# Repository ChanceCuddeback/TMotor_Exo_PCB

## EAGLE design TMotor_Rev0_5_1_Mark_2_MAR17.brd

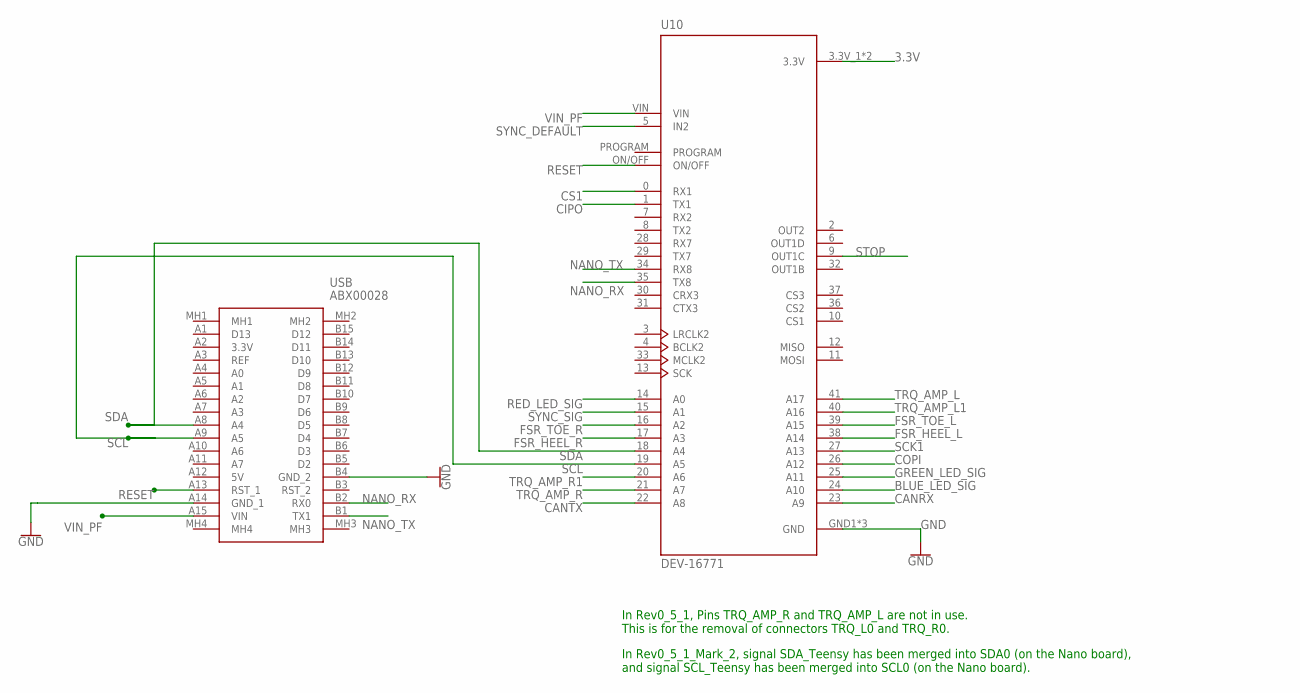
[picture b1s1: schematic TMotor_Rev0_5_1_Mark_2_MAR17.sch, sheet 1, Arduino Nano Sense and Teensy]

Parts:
U10: DEV-16771; MODULE_DEV-16771
USB: ABX00028

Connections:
3.3V: U10.3.3V_1 (3.3V), U10.3.3V_2 (3.3V); also elsewhere on the board
BLUE_LED_SIG: U10.24 (A10); also elsewhere on the board
CANRX: U10.23 (A9); also elsewhere on the board
CANTX: U10.22 (A8); also elsewhere on the board
CIPO: U10.1 (TX1); also elsewhere on the board
COPI: U10.26 (A12); also elsewhere on the board
CS1: U10.0 (RX1); also elsewhere on the board
FSR_HEEL_L: U10.38 (A14); also elsewhere on the board
FSR_HEEL_R: U10.17 (A3); also elsewhere on the board
FSR_TOE_L: U10.39 (A15); also elsewhere on the board
FSR_TOE_R: U10.16 (A2); also elsewhere on the board
GND: U10.GND1 (GND), U10.GND2 (GND), U10.GND3 (GND), USB.A14 (GND_1), USB.B4 (GND_2); also elsewhere on the board
GREEN_LED_SIG: U10.25 (A11); also elsewhere on the board
NANO_RX: U10.35 (TX8), USB.B2 (RX0)
NANO_TX: U10.34 (RX8), USB.B1 (TX1)
RED_LED_SIG: U10.14 (A0); also elsewhere on the board
RESET: U10.ON/OFF, USB.A13 (RST_1); also elsewhere on the board
SCK1: U10.27 (A13); also elsewhere on the board
SCL: U10.19 (A5), USB.A9 (A5); also elsewhere on the board
SDA: U10.18 (A4), USB.A8 (A4); also elsewhere on the board
STOP: U10.9 (OUT1C); also elsewhere on the board
SYNC_DEFAULT: U10.5 (IN2); also elsewhere on the board
SYNC_SIG: U10.15 (A1); also elsewhere on the board
TRQ_AMP_L: U10.41 (A17)
TRQ_AMP_L1: U10.40 (A16); also elsewhere on the board
TRQ_AMP_R: U10.21 (A7)
TRQ_AMP_R1: U10.20 (A6); also elsewhere on the board
VIN_PF: U10.VIN, USB.A15 (VIN); also elsewhere on the board

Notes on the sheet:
In Rev0_5_1, Pins TRQ_AMP_R and TRQ_AMP_L are not in use. This is for the removal of connectors TRQ_L0 and TRQ_R0.
In Rev0_5_1_Mark_2, signal SDA_Teensy has been merged into SDA0 (on the Nano board), and signal SCL_Teensy has been merged into SCL0 (on the Nano board).

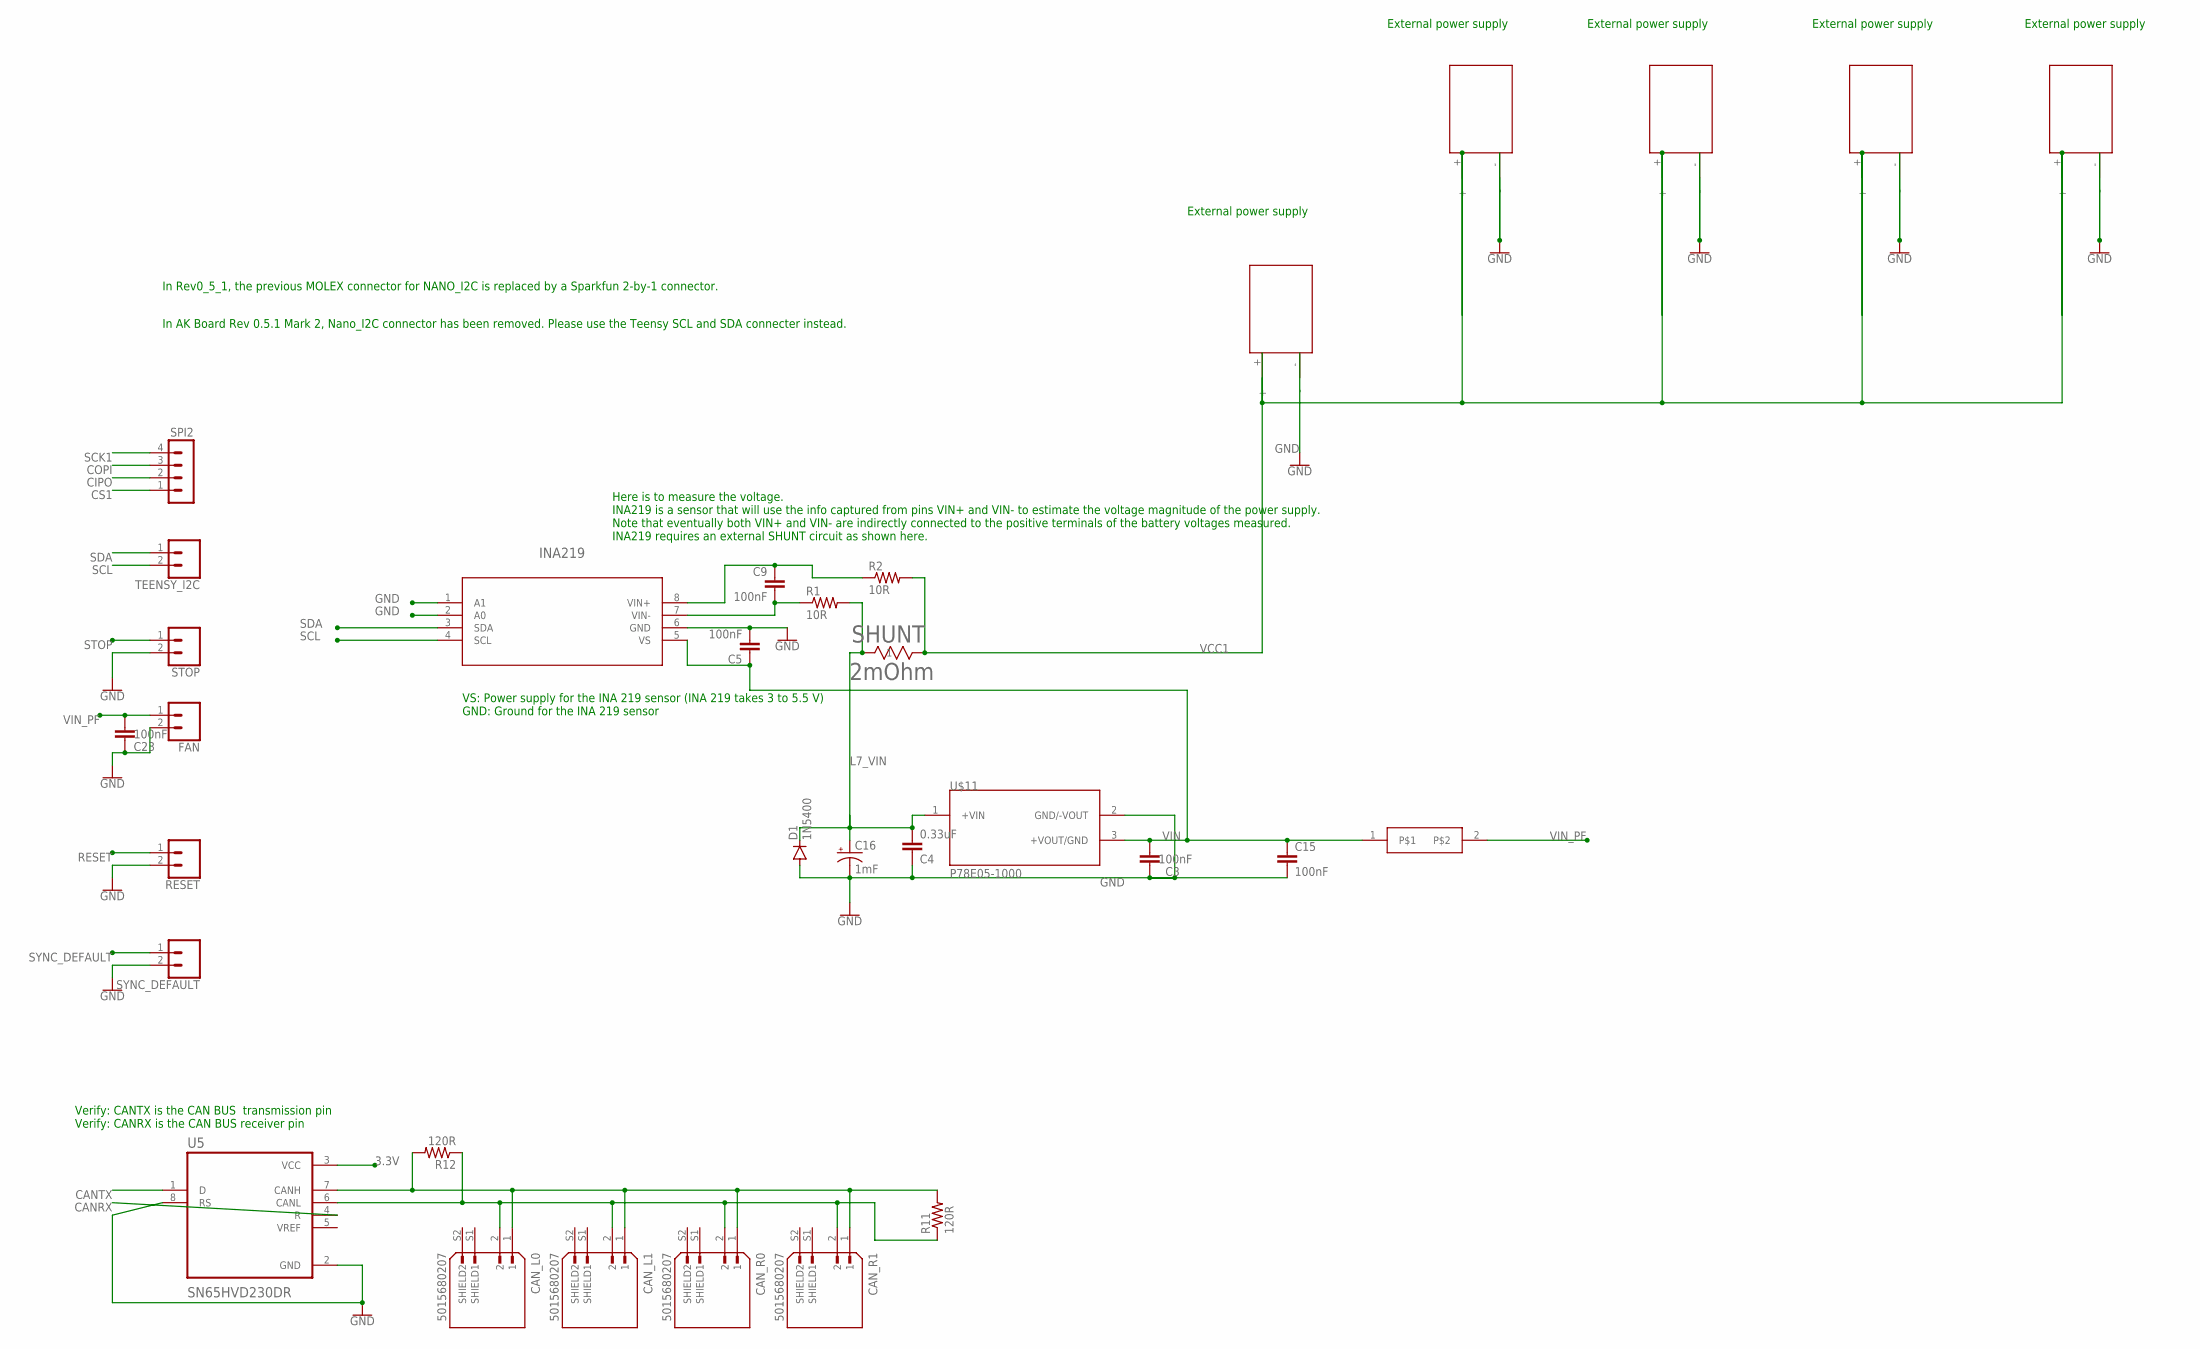
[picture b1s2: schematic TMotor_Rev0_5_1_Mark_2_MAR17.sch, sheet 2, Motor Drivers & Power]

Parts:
C3, C5, C9, C15, C23: 100nF; C050-024X044
C4: 0.33uF; C050-024X044
C16: 1mF; E5-10,5
CAN_L0, CAN_L1: 5015680207; MOLEX_5015680207
CAN_R0, CAN_R1: 5015680207; MOLEX_5015680207
D1: 1N5400; DO201-15
FAN: CONN_02; 1X02
INA219: D8_TEX
R1, R2: 10R; 0207/10
R11, R12: 120R; 0207/10
RESET: CONN_02; 1X02
SHUNT: 2mOhm; STA_CSNL2512(2)_STP
SPI2: MA04-1
STOP: CONN_02; 1X02
SYNC_DEFAULT: CONN_02; 1X02
TEENSY_I2C: CONN_02; 1X02
U5: SN65HVD230DR; SOIC127P599X175-8N
U$6: 0458002.DR; FUSE_LITTEL_448
U$11: P78E05-1000
XT30UPB-F, XT30UPB-F1, XT30UPB-F2, XT30UPB-F3, XT30UPB-F4: L_0; XT30UPB-F

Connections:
3.3V: U5.3 (VCC); also elsewhere on the board
CANRX: U5.4 (R); also elsewhere on the board
CANTX: U5.1 (D); also elsewhere on the board
CIPO: SPI2.2; also elsewhere on the board
COPI: SPI2.3; also elsewhere on the board
CS1: SPI2.1; also elsewhere on the board
GND: C3.1, C4.1, C5.2, C15.2, C16.-, C23.1, D1.A, FAN.2, INA219.1 (A1), INA219.2 (A0), INA219.6 (GND), RESET.2, STOP.2, SYNC_DEFAULT.2, U5.2 (GND), U5.8 (RS), U$11.2 (GND/-VOUT), XT30UPB-F.-, XT30UPB-F1.-, XT30UPB-F2.-, XT30UPB-F3.-, XT30UPB-F4.-; also elsewhere on the board
L7_VIN: C4.2, C16.+, D1.C, R1.2, SHUNT.1, U$11.1 (+VIN)
unnamed: C9.1, INA219.8 (VIN+), R2.1
unnamed: C9.2, INA219.7 (VIN-), R1.1
unnamed: CAN_L0.1, CAN_L1.1, CAN_R0.1, CAN_R1.1, R11.2, R12.2, U5.7 (CANH)
unnamed: CAN_L0.2, CAN_L1.2, CAN_R0.2, CAN_R1.2, R11.1, R12.1, U5.6 (CANL)
RESET: RESET.1; also elsewhere on the board
SCK1: SPI2.4; also elsewhere on the board
SCL: INA219.4 (SCL), TEENSY_I2C.2; also elsewhere on the board
SDA: INA219.3 (SDA), TEENSY_I2C.1; also elsewhere on the board
STOP: STOP.1; also elsewhere on the board
SYNC_DEFAULT: SYNC_DEFAULT.1; also elsewhere on the board
VCC1: R2.2, SHUNT.2, XT30UPB-F.+, XT30UPB-F1.+, XT30UPB-F2.+, XT30UPB-F3.+, XT30UPB-F4.+
VIN: C3.2, C5.1, C15.1, INA219.5 (VS), U$6.1, U$11.3 (+VOUT/GND)
VIN_PF: C23.2, FAN.1, U$6.2; also elsewhere on the board

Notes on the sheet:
External power supply
Here is to measure the voltage. INA219 is a sensor that will use the info captured from pins VIN+ and VIN- to estimate the voltage magnitude of the power supply. Note that eventually both VIN+ and VIN- are indirectly connected to the positive terminals of the battery voltages measured. INA219 requi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
VS: Power supply for the INA 219 sensor (INA 219 takes 3 to 5.5 V) GND: Ground for the INA 219 sensor
Verify: CANTX is the CAN BUS transmission pin Verify: CANRX is the CAN BUS receiver pin
In Rev0_5_1, the previous MOLEX connector for NANO_I2C is replaced by a Sparkfun 2-by-1 connector.
In AK Board Rev 0.5.1 Mark 2, Nano_I2C connector has been removed. Please use the Teensy SCL and SDA connecter instead.

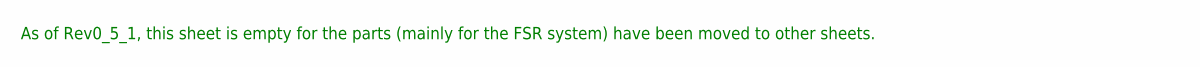
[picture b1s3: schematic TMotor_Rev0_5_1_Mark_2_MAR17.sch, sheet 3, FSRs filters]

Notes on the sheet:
As of Rev0_5_1, this sheet is empty for the parts (mainly for the FSR system) have been moved to other sheets.

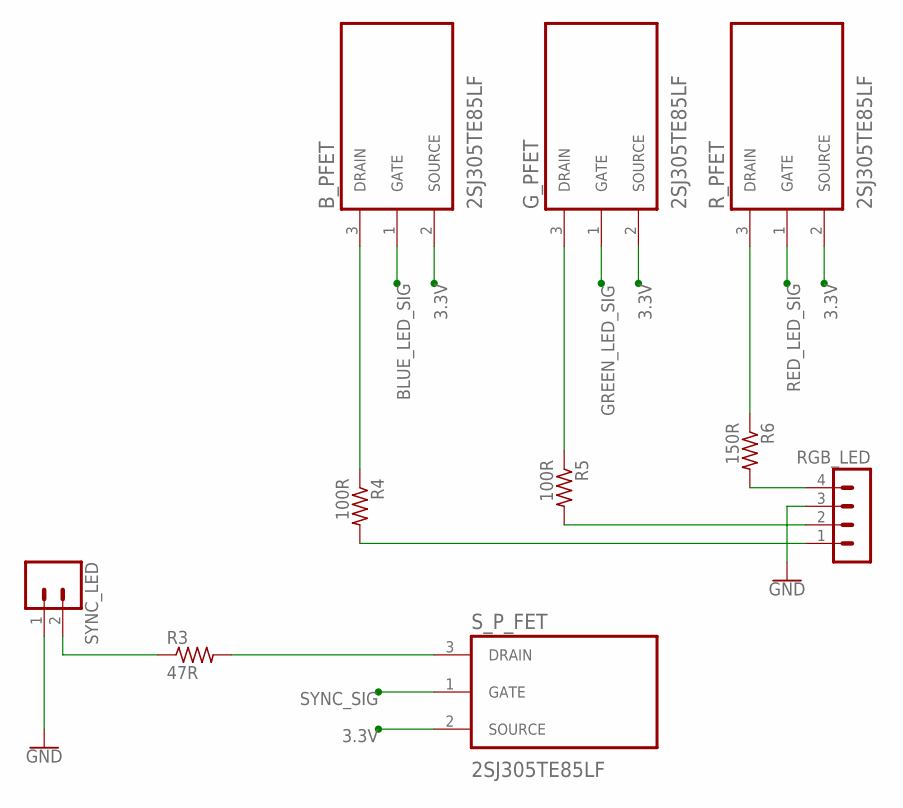
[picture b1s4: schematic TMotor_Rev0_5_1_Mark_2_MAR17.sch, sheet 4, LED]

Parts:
B_PFET: 2SJ305TE85LF; TRANS_SSM3J325F,LF
G_PFET: 2SJ305TE85LF; TRANS_SSM3J325F,LF
R3: 47R; 0207/10
R4, R5: 100R; 0207/10
R6: 150R; 0207/10
RGB_LED: MA04-1
R_PFET: 2SJ305TE85LF; TRANS_SSM3J325F,LF
SYNC_LED: CONN_02; 1X02
S_P_FET: 2SJ305TE85LF; TRANS_SSM3J325F,LF

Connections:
3.3V: B_PFET.2 (SOURCE), G_PFET.2 (SOURCE), R_PFET.2 (SOURCE), S_P_FET.2 (SOURCE); also elsewhere on the board
BLUE_LED_SIG: B_PFET.1 (GATE); also elsewhere on the board
GND: RGB_LED.3, SYNC_LED.1; also elsewhere on the board
GREEN_LED_SIG: G_PFET.1 (GATE); also elsewhere on the board
unnamed: R4.2, RGB_LED.1
unnamed: B_PFET.3 (DRAIN), R4.1
unnamed: R3.2, S_P_FET.3 (DRAIN)
unnamed: R3.1, SYNC_LED.2
unnamed: R6.2, RGB_LED.4
unnamed: R5.2, RGB_LED.2
unnamed: G_PFET.3 (DRAIN), R5.1
unnamed: R6.1, R_PFET.3 (DRAIN)
RED_LED_SIG: R_PFET.1 (GATE); also elsewhere on the board
SYNC_SIG: S_P_FET.1 (GATE); also elsewhere on the board

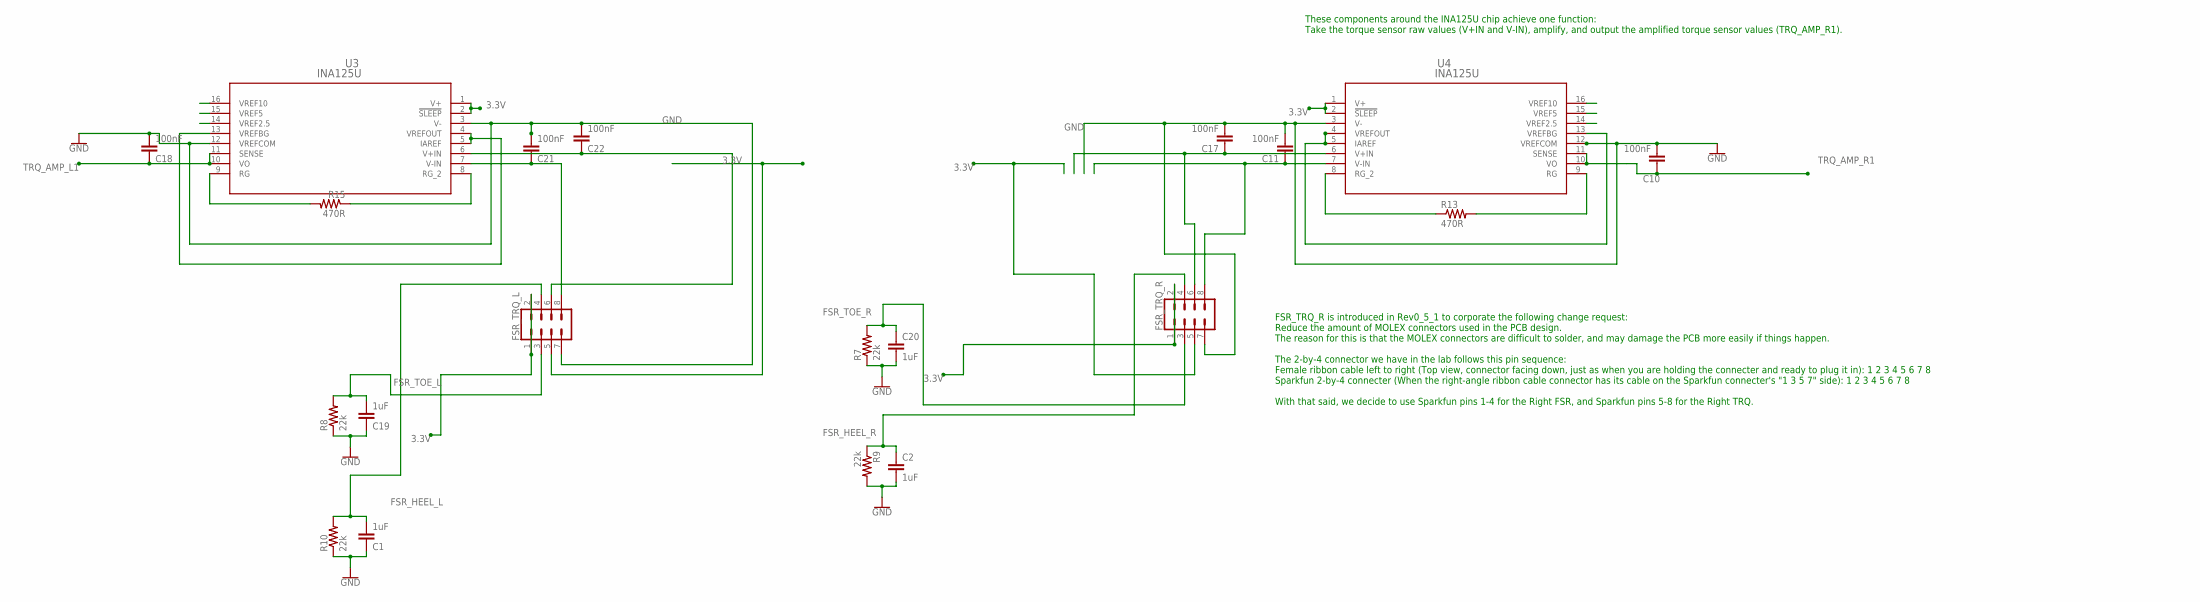
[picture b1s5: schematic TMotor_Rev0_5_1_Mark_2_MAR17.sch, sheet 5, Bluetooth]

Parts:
C1, C2, C19, C20: 1uF; C050-024X044
C10, C11, C17, C18, C21, C22: 100nF; C050-024X044
FSR_TRQ_L: CONN_04X2; 2X4
FSR_TRQ_R: CONN_04X2; 2X4
R7, R8, R9, R10: 22k; 0207/10
R13, R15: 470R; 0207/10
U3, U4: INA125U; D16

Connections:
3.3V: FSR_TRQ_L.1, FSR_TRQ_L.2, FSR_TRQ_L.5, FSR_TRQ_R.1, FSR_TRQ_R.2, FSR_TRQ_R.5, U3.1 (V+), U3.2 (!SLEEP), U4.1 (V+), U4.2 (!SLEEP); also elsewhere on the board
FSR_HEEL_L: C1.2, FSR_TRQ_L.4, R10.2; also elsewhere on the board
FSR_HEEL_R: C2.1, FSR_TRQ_R.4, R9.1; also elsewhere on the board
FSR_TOE_L: C19.2, FSR_TRQ_L.3, R8.2; also elsewhere on the board
FSR_TOE_R: C20.1, FSR_TRQ_R.3, R7.2; also elsewhere on the board
GND: C1.1, C2.2, C10.2, C11.2, C17.2, C18.2, C19.1, C20.2, C21.2, C22.2, FSR_TRQ_L.7, FSR_TRQ_R.7, R7.1, R8.1, R9.2, R10.1, U3.3 (V-), U3.12 (VREFCOM), U4.3 (V-), U4.12 (VREFCOM); also elsewhere on the board
unnamed: U4.4 (VREFOUT), U4.5 (IAREF), U4.13 (VREFBG)
unnamed: R13.1, U4.8 (RG_2)
unnamed: R13.2, U4.9 (RG)
unnamed: C17.1, FSR_TRQ_R.6, U4.6 (V+IN)
unnamed: C11.1, FSR_TRQ_R.8, U4.7 (V-IN)
unnamed: U3.4 (VREFOUT), U3.5 (IAREF), U3.13 (VREFBG)
unnamed: C22.1, FSR_TRQ_L.6, U3.6 (V+IN)
unnamed: C21.1, FSR_TRQ_L.8, U3.7 (V-IN)
unnamed: R15.2, U3.9 (RG)
unnamed: R15.1, U3.8 (RG_2)
TRQ_AMP_L1: C18.1, U3.10 (VO), U3.11 (SENSE); also elsewhere on the board
TRQ_AMP_R1: C10.1, U4.10 (VO), U4.11 (SENSE); also elsewhere on the board

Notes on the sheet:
FSR_TRQ_R is introduced in Rev0_5_1 to corporate the following change request: Reduce the amount of MOLEX connectors used in the PCB design. The reason for this is that the MOLEX connectors are difficult to solder, and may damage the PCB more easily if things happen. The 2-by-4 connector we have in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
These components around the INA125U chip achieve one function: Take the torque sensor raw values (V+IN and V-IN), amplify, and output the amplified torque sensor values (TRQ_AMP_R1).

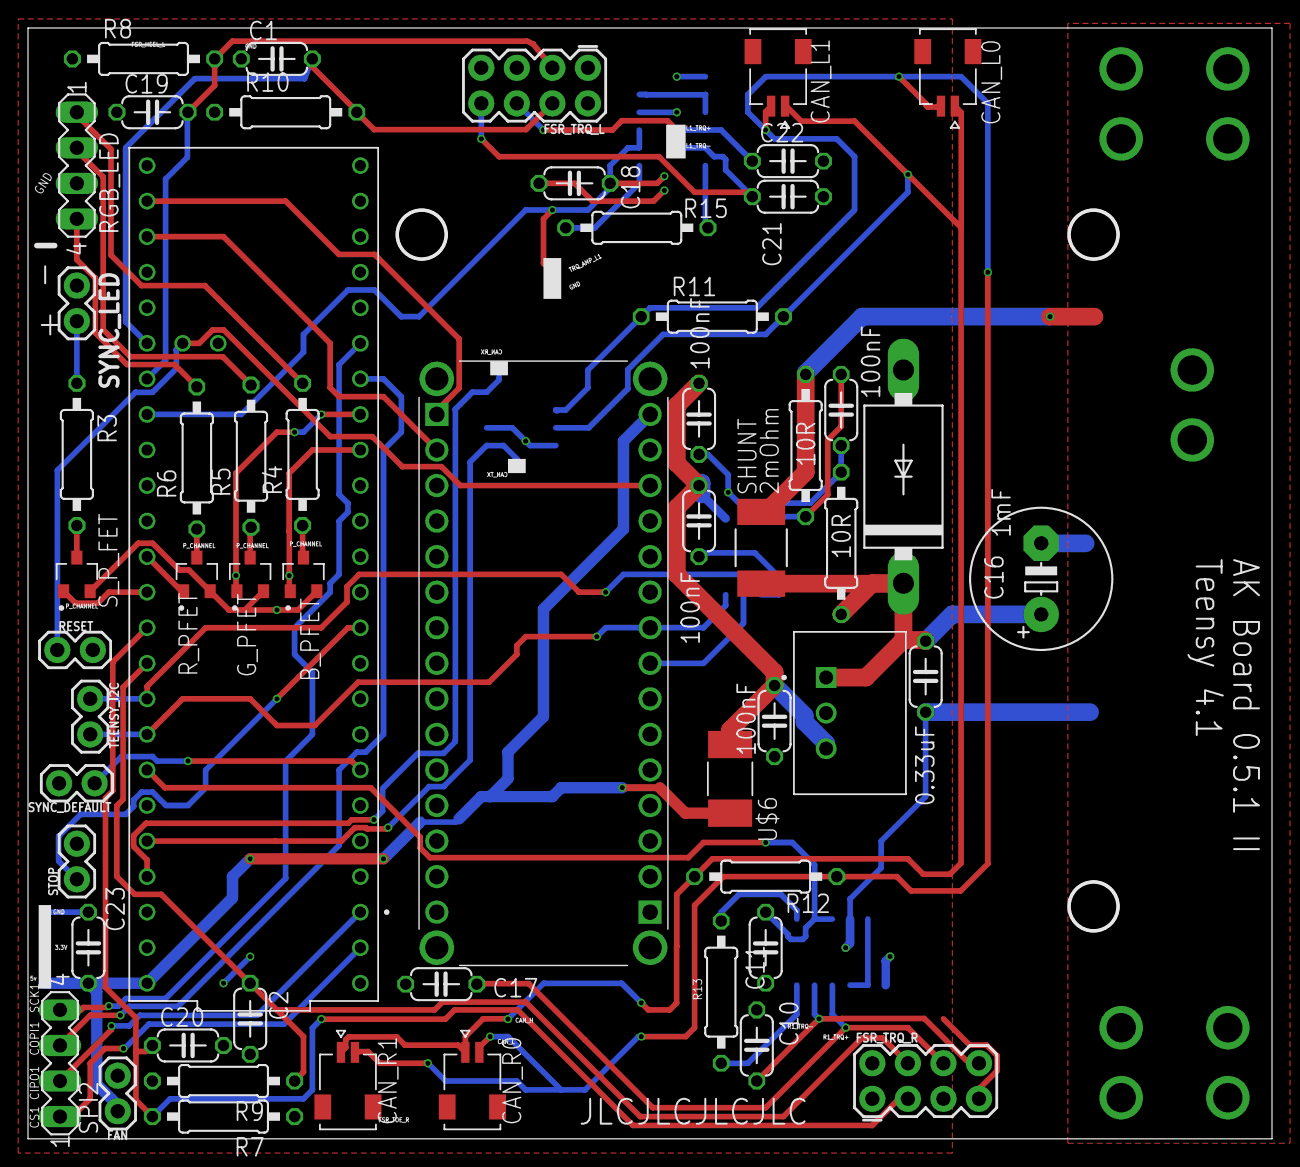
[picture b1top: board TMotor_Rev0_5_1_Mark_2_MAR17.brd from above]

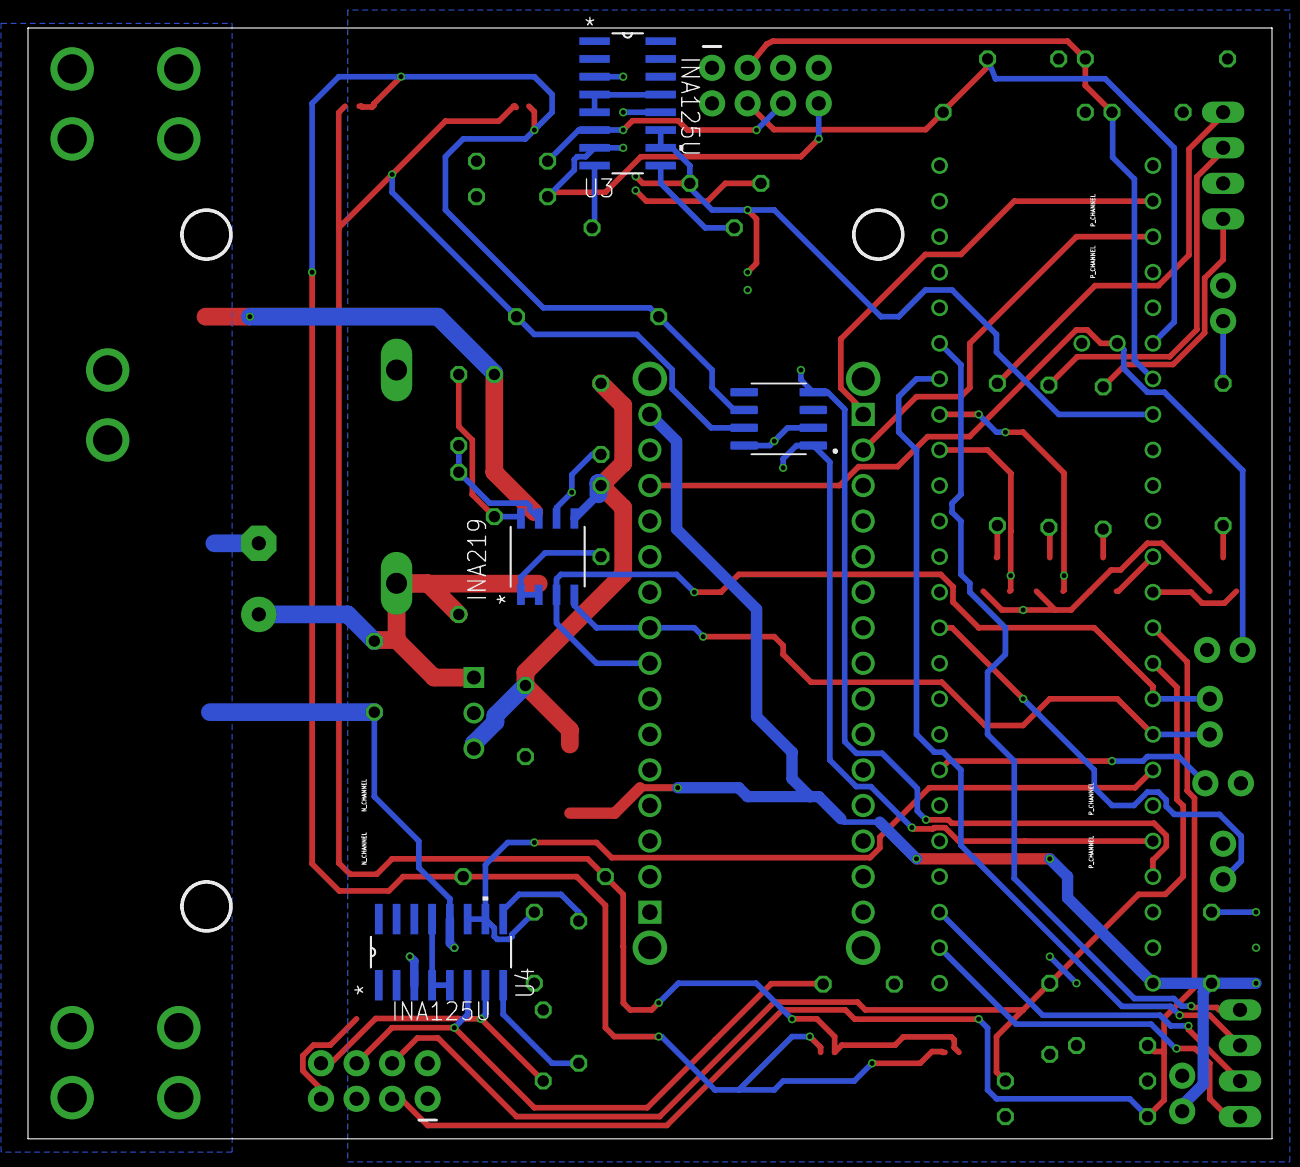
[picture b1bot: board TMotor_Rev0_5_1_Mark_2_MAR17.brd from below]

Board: 2 copper layers, 88.6 x 79.1 mm, 64 parts (4 on the bottom side), 51 nets.

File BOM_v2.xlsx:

Comments | Designator | Footprint | JLCPCB Part #（optional）
2SJ305TE85LF | B_PFET | 2SJ305TE85LF | C694088
1uF | C1 | C-EU050-024X044 | C263187
1uF | C2 | C-EU050-024X044 | C263187
100nF | C3 | C-EU050-024X044 | C110282
0.33uF | C4 | C-EU050-024X044 | C454383
100nF | C5 | C-EU050-024X044 | C110282
100nF | C9 | C-EU050-024X044 | C110282
100nF | C10 | C-EU050-024X044 | C110282
100nF | C11 | C-EU050-024X044 | C110282
100nF | C15 | C-EU050-024X044 | C110282
1mF | C16 | CPOL-USE5-10.5 | C44595
100nF | C17 | C-EU050-024X044 | C110282
100nF | C18 | C-EU050-024X044 | C110282
1uF | C19 | C-EU050-024X044 | C263187
1uF | C20 | C-EU050-024X044 | C263187
100nF | C21 | C-EU050-024X044 | C110282
100nF | C22 | C-EU050-024X044 | C110282
100nF | C23 | C-EU050-024X044 | C110282
5015680207 | CAN_L0 | 5015680207
5015680207 | CAN_L1 | 5015680207
5015680207 | CAN_R0 | 5015680207
5015680207 | CAN_R1 | 5015680207
1N5400 | D1 | 1N5400 | C263136
CONN_02 | FAN | 1X02 | C5156429
CONN_04X2 | FSR_TRQ_L | 2X4 | C706894
CONN_04X2 | FSR_TRQ_R | 2X4 | C706894
2SJ305TE85LF | G_PFET | 2SJ305TE85LF | C694088
INA219AIDR | INA219 | D8_TEX | C138706
CONN_02 | NANO_I2C | 1X02 | C5156429
10R | R1 | R-US_0207/10 | C385442
10R | R2 | R-US_0207/10 | C385442
47R | R3 | R-US_0207/10 | C385516
100R | R4 | R-US_0207/10 | C433533
100R | R5 | R-US_0207/10 | C433533
150R | R6 | R-US_0207/10 | C385454
22k | R7 | R-US_0207/10 | C385475
22k | R8 | R-US_0207/10 | C385475
22k | R9 | R-US_0207/10 | C385475
22k | R10 | R-US_0207/10 | C385475
120R | R11 | R-US_0207/10 | C385447
120R | R12 | R-US_0207/10 | C385447
CONN_02 | RESET | 1X02 | C5156429
MA04-1 | RGB_LED | MA04-1 | C5156431
2SJ305TE85LF | R_PFET | 2SJ305TE85LF | C694088
2mOhm | SHUNT | CSNL2512FT2L00 | C335242
MA04-1 | SPI2 | MA04-1 | C5156431
CONN_02 | STOP | 1X02 | C5156429
CONN_02 | SYNC_DEFAULT | 1X02 | C5156429
CONN_02 | SYNC_LED | 1X02 | C5156429
2SJ305TE85LF | S_P_FET | 2SJ305TE85LF | C694088
CONN_02 | TEENSY_I2C | 1X02 | C5156429
0458002.DR | U$6 | 0458002.DR | C5220731
P78E05-1000 | U$11 | P78E05-1000
INA125U | U3 | INA125U
INA125U | U4 | INA125U
SN65HVD230MDREP | U5 | SN65HVD230MDREP
DEV-16771 | U10 | DEV-16771
ABX00028 | USB | ABX00028 | C2897378
L_0 | XT30UPB-F | XT30UPB-F | C108769
L_0 | XT30UPB-F1 | XT30UPB-F | C108769
L_0 | XT30UPB-F2 | XT30UPB-F | C108769
L_0 | XT30UPB-F3 | XT30UPB-F | C108769
L_0 | XT30UPB-F4 | XT30UPB-F | C108769
ABX00028 | USB | ABX00028 | C2897378

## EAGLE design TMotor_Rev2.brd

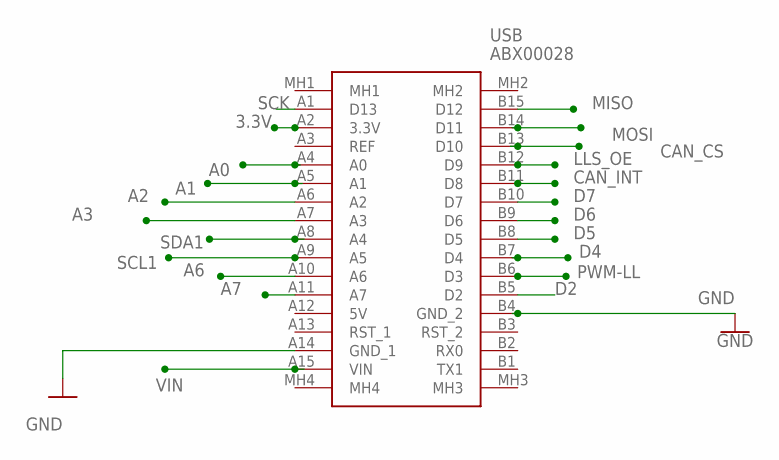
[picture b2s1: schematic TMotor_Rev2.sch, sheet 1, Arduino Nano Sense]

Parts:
USB: ABX00028

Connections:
3.3V: USB.A2 (3.3V); also elsewhere on the board
A0: USB.A4 (A0); also elsewhere on the board
A1: USB.A5 (A1)
A2: USB.A6 (A2); also elsewhere on the board
A3: USB.A7 (A3); also elsewhere on the board
A6: USB.A10 (A6); also elsewhere on the board
A7: USB.A11 (A7)
CAN_CS: USB.B13 (D10); also elsewhere on the board
CAN_INT: USB.B11 (D8); also elsewhere on the board
D2: USB.B5 (D2); also elsewhere on the board
D4: USB.B7 (D4)
D5: USB.B8 (D5)
D6: USB.B9 (D6)
D7: USB.B10 (D7)
GND: USB.A14 (GND_1), USB.B4 (GND_2); also elsewhere on the board
LLS_OE: USB.B12 (D9)
MISO: USB.B15 (D12); also elsewhere on the board
MOSI: USB.B14 (D11); also elsewhere on the board
PWM-LL: USB.B6 (D3)
SCK: USB.A1 (D13); also elsewhere on the board
SCL1: USB.A9 (A5)
SDA1: USB.A8 (A4)
VIN: USB.A15 (VIN); also elsewhere on the board

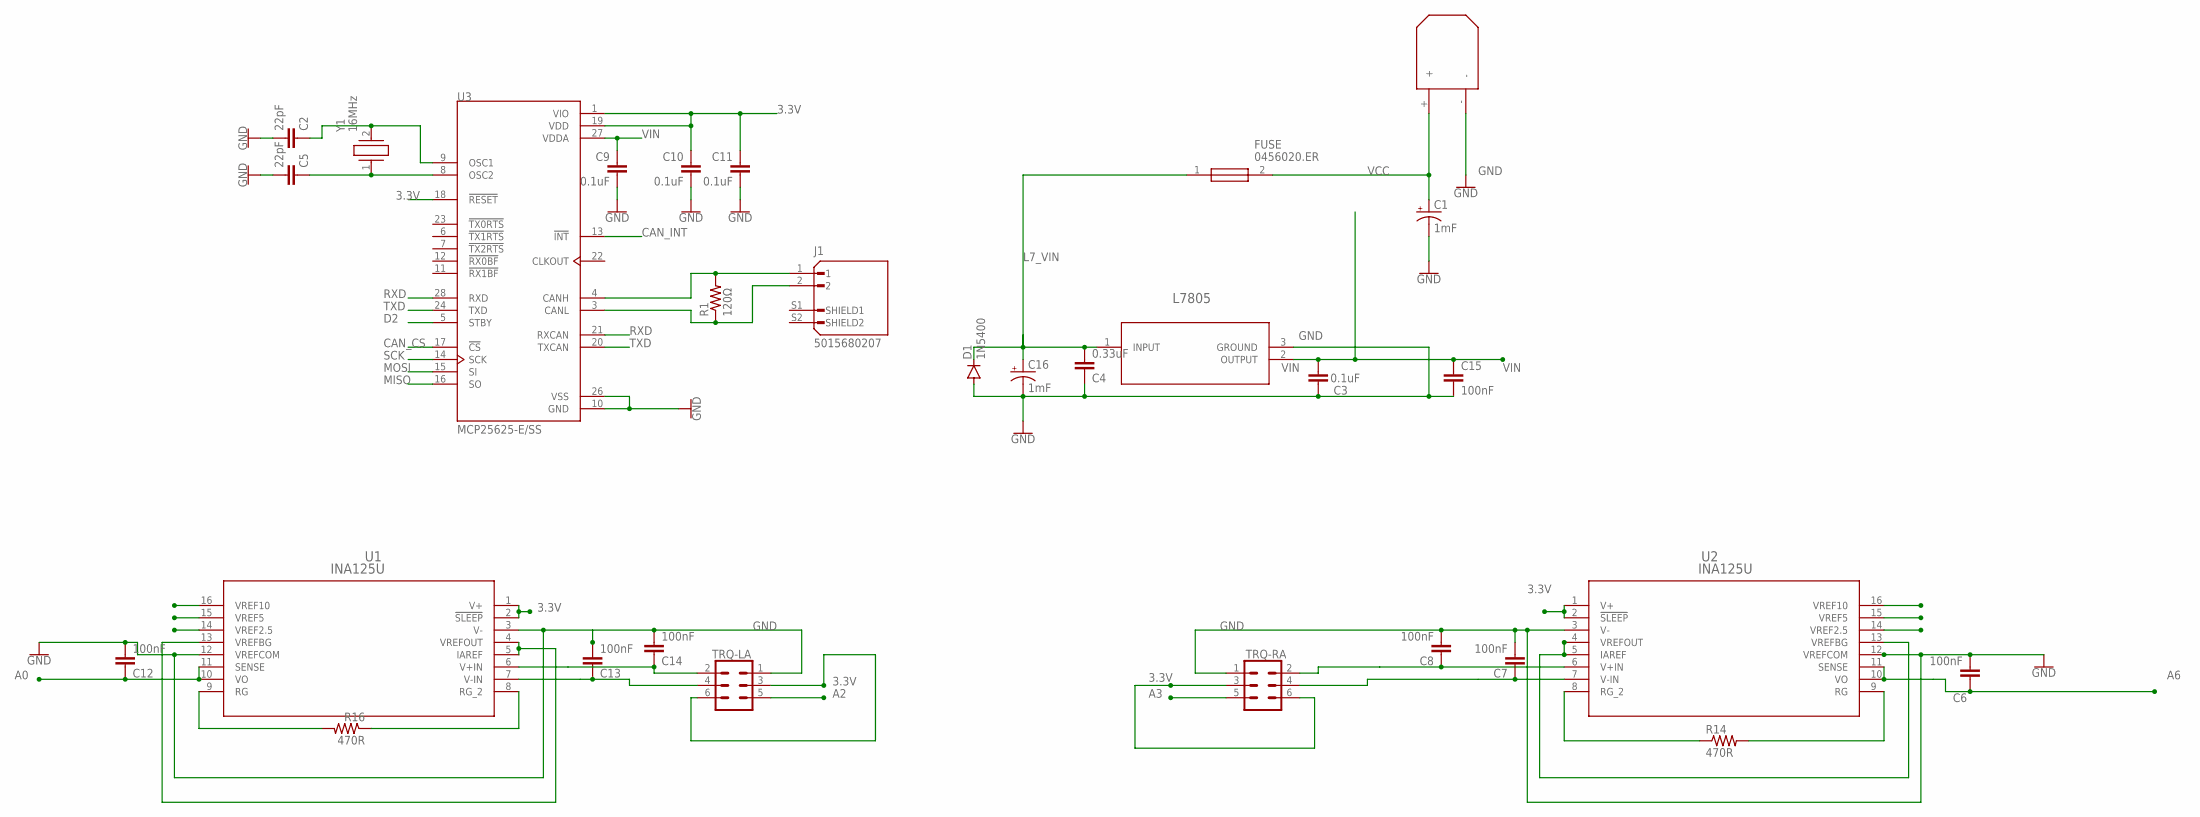
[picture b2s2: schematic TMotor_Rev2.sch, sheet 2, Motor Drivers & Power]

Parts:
C1, C16: 1mF; E5-10,5
C2, C5: 22pF; C050-024X044
C3, C9, C10, C11: 0.1uF; C050-024X044
C4: 0.33uF; C050-024X044
C6, C7, C8, C12, C13, C14, C15: 100nF; C050-024X044
D1: 1N5400; DO201-15
FUSE: 0456020.ER; FUSC10131X312N
J1: 5015680207; MOLEX_5015680207
L7805: DPAK_STM
R1: 120Ω; 0207/10
R14, R16: 470R; 0207/10
TRQ-LA: CONN_03X2SHROUD; 2X3-SHROUDED
TRQ-RA: CONN_03X2SHROUD; 2X3-SHROUDED
U1, U2: INA125U; D16
U3: MCP25625-E/SS; SOP65P780X200-28N
U$9: XT30; XT30_HORIZONTAL
Y1: 16MHz; IQD-HC-49-4H

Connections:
3.3V: C10.1, C11.1, TRQ-LA.3, TRQ-LA.6, TRQ-RA.3, TRQ-RA.6, U1.1 (V+), U1.2 (!SLEEP), U2.1 (V+), U2.2 (!SLEEP), U3.1 (VIO), U3.18 (!RESET), U3.19 (VDD); also elsewhere on the board
A0: C12.1, U1.10 (VO), U1.11 (SENSE); also elsewhere on the board
A2: TRQ-LA.5; also elsewhere on the board
A3: TRQ-RA.5; also elsewhere on the board
A6: C6.1, U2.10 (VO), U2.11 (SENSE); also elsewhere on the board
CANH-: J1.1, R1.2, U3.4 (CANH)
CANL-: J1.2, R1.1, U3.3 (CANL)
CAN_CS: U3.17 (!CS); also elsewhere on the board
CAN_INT: U3.13 (!INT); also elsewhere on the board
D2: U3.5 (STBY); also elsewhere on the board
GND: C1.-, C2.2, C3.1, C4.1, C5.2, C6.2, C7.2, C8.2, C9.2, C10.2, C11.2, C12.2, C13.2, C14.2, C15.2, C16.-, D1.A, L7805.3 (GROUND), TRQ-LA.1, TRQ-RA.1, U1.3 (V-), U1.12 (VREFCOM), U2.3 (V-), U2.12 (VREFCOM), U3.10 (GND), U3.26 (VSS), U$9.-; also elsewhere on the board
L7_VIN: C4.2, C16.+, D1.C, FUSE.1, L7805.1 (INPUT)
MISO: U3.16 (SO); also elsewhere on the board
MOSI: U3.15 (SI); also elsewhere on the board
unnamed: C2.1, U3.9 (OSC1), Y1.2
unnamed: C5.1, U3.8 (OSC2), Y1.1
unnamed: U1.4 (VREFOUT), U1.5 (IAREF), U1.13 (VREFBG)
unnamed: U2.4 (VREFOUT), U2.5 (IAREF), U2.13 (VREFBG)
unnamed: R14.1, U2.8 (RG_2)
unnamed: R14.2, U2.9 (RG)
unnamed: C8.1, TRQ-RA.2, U2.6 (V+IN)
unnamed: C7.1, TRQ-RA.4, U2.7 (V-IN)
unnamed: C14.1, TRQ-LA.2, U1.6 (V+IN)
unnamed: C13.1, TRQ-LA.4, U1.7 (V-IN)
unnamed: R16.2, U1.9 (RG)
unnamed: R16.1, U1.8 (RG_2)
RXD: U3.21 (RXCAN), U3.28 (RXD)
SCK: U3.14 (SCK); also elsewhere on the board
TXD: U3.20 (TXCAN), U3.24 (TXD)
VCC: C1.+, FUSE.2, U$9.+
VIN: C3.2, C9.1, C15.1, L7805.2 (OUTPUT), U3.27 (VDDA); also elsewhere on the board

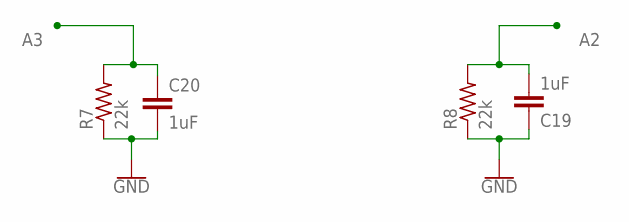
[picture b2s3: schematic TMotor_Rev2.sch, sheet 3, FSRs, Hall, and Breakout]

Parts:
C19, C20: 1uF; C050-024X044
R7, R8: 22k; 0207/10

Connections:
A2: C19.2, R8.2; also elsewhere on the board
A3: C20.1, R7.2; also elsewhere on the board
GND: C19.1, C20.2, R7.1, R8.1; also elsewhere on the board

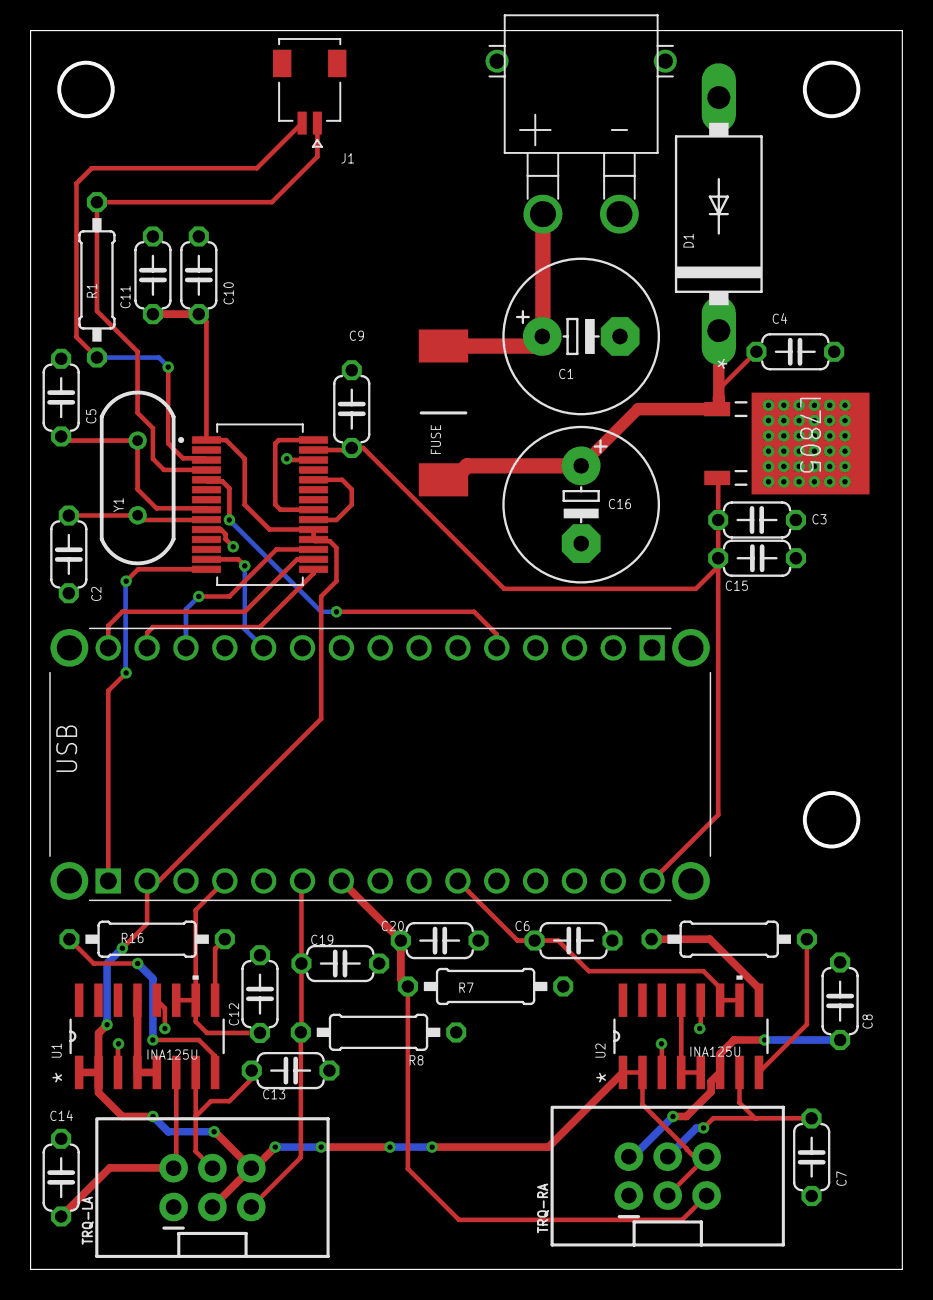
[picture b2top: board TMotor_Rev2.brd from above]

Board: 2 copper layers, 56.7 x 80.7 mm, 35 parts (0 on the bottom side), 31 nets.

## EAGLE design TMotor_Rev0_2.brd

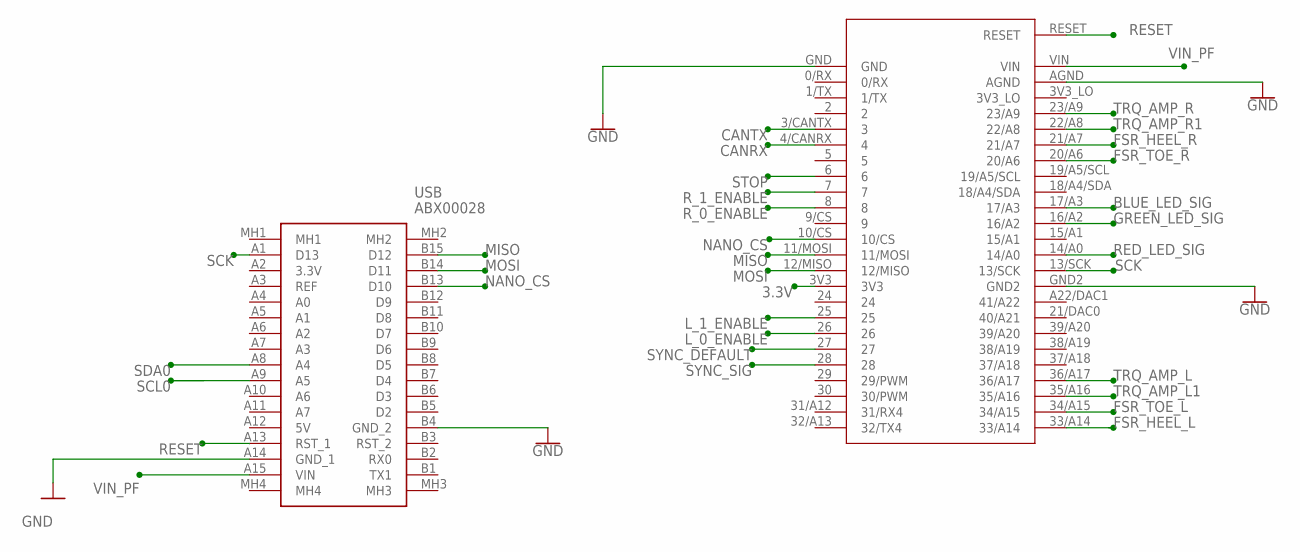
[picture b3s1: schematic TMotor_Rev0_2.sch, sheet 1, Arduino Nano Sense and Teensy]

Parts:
U$1: TEENSY_3.5/3.6_EXTERNAL_W/RESET
USB: ABX00028

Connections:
3.3V: U$1.3V3; also elsewhere on the board
BLUE_LED_SIG: U$1.17/A3; also elsewhere on the board
CANRX: U$1.4/CANRX (4); also elsewhere on the board
CANTX: U$1.3/CANTX (3); also elsewhere on the board
FSR_HEEL_L: U$1.33/A14; also elsewhere on the board
FSR_HEEL_R: U$1.21/A7; also elsewhere on the board
FSR_TOE_L: U$1.34/A15; also elsewhere on the board
FSR_TOE_R: U$1.20/A6; also elsewhere on the board
GND: U$1.AGND, U$1.GND, U$1.GND2, USB.A14 (GND_1), USB.B4 (GND_2); also elsewhere on the board
GREEN_LED_SIG: U$1.16/A2; also elsewhere on the board
L_0_ENABLE: U$1.26; also elsewhere on the board
L_1_ENABLE: U$1.25; also elsewhere on the board
MISO: U$1.11/MOSI, USB.B15 (D12)
MOSI: U$1.12/MISO, USB.B14 (D11)
NANO_CS: U$1.10/CS, USB.B13 (D10)
RED_LED_SIG: U$1.14/A0; also elsewhere on the board
RESET: U$1.RESET, USB.A13 (RST_1); also elsewhere on the board
R_0_ENABLE: U$1.8; also elsewhere on the board
R_1_ENABLE: U$1.7; also elsewhere on the board
SCK: U$1.13/SCK, USB.A1 (D13)
SCL0: USB.A9 (A5); also elsewhere on the board
SDA0: USB.A8 (A4); also elsewhere on the board
STOP: U$1.6; also elsewhere on the board
SYNC_DEFAULT: U$1.27; also elsewhere on the board
SYNC_SIG: U$1.28; also elsewhere on the board
TRQ_AMP_L: U$1.36/A17; also elsewhere on the board
TRQ_AMP_L1: U$1.35/A16; also elsewhere on the board
TRQ_AMP_R: U$1.23/A9; also elsewhere on the board
TRQ_AMP_R1: U$1.22/A8; also elsewhere on the board
VIN_PF: U$1.VIN, USB.A15 (VIN); also elsewhere on the board

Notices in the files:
parts and their libraries:
SparkFun-Connectors: Licensing: Creative Commons ShareAlike 4.0 International - https://creativecommons.org/licenses/by-sa/4.0
microbuilder: This work is placed in the public domain, and may be freely used for commercial and non-commercial work with the following conditions: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
